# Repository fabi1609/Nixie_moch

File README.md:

# Nixie_moch

You are not permitted to use this design commercially.
This work is licensed under a Attribution-NonCommercial-ShareAlike 4.0 International (CC BY-NC-SA 4.0) License.

## Description

This is a tiny IN-12 Nixie clock based on STM32. Every SMD component is placed on the bottom side of the PCB. Hardware works with 5 V USB power supply. Boost converter is regulated and driven by STM32.
This project is in beta phase.

## TODO: Write explanation

You are not permitted to use this design commercially.
This work is licensed under a Attribution-NonCommercial-ShareAlike 4.0 International (CC BY-NC-SA 4.0) License.

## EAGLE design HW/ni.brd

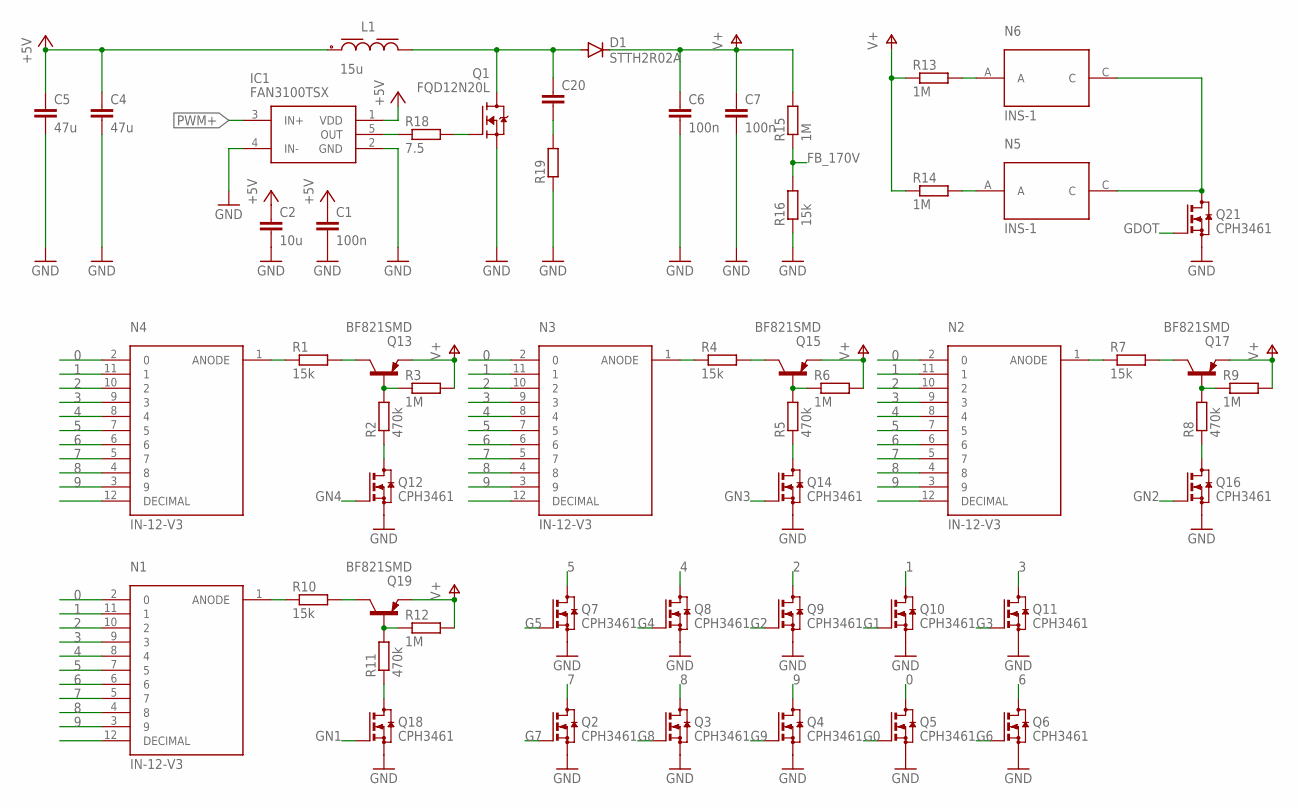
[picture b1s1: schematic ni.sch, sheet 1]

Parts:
C1: 100n; C0402
C2: 10u; C1206
C4, C5: 47u; C1206
C6, C7: 100n; C1812
C20: C-EUC1206; C1206
D1: STTH2R02A; DO214AC
IC1: FAN3100TSX; SOT95P280X145-5N
L1: 15u; WE-LQS_5040
N1, N2, N3, N4: IN-12-V3; IN-12
N5, N6: INS-1
Q1: FQD12N20L; TO229P990X240-3N
Q2, Q3, Q4, Q5, Q6, Q7, Q8, Q9, Q10, Q11, Q12, Q14, Q16, Q18, Q21: CPH3461; SOT23
Q13, Q15, Q17, Q19: BF821SMD; SOT23-BEC
R1, R4, R7, R10: 15k; R1206
R2, R5, R8, R11: 470k; R1206
R3, R6, R9, R12, R15: 1M; R1206
R13, R14: 1M; R2010
R16: 15k; R0402
R18: 7.5; R0603
R19: R-EU_R1206; R1206

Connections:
0: N1.2 (0), N2.2 (0), N3.2 (0), N4.2 (0), Q5.3 (D)
1: N1.11 (1), N2.11 (1), N3.11 (1), N4.11 (1), Q10.3 (D)
2: N1.10 (2), N2.10 (2), N3.10 (2), N4.10 (2), Q9.3 (D)
3: N1.9 (3), N2.9 (3), N3.9 (3), N4.9 (3), Q11.3 (D)
4: N1.8 (4), N2.8 (4), N3.8 (4), N4.8 (4), Q8.3 (D)
5: N1.7 (5), N2.7 (5), N3.7 (5), N4.7 (5), Q7.3 (D)
6: N1.6, N2.6, N3.6, N4.6, Q6.3 (D)
7: N1.5 (7), N2.5 (7), N3.5 (7), N4.5 (7), Q2.3 (D)
8: N1.4 (8), N2.4 (8), N3.4 (8), N4.4 (8), Q3.3 (D)
9: N1.3 (9), N2.3 (9), N3.3 (9), N4.3 (9), Q4.3 (D)
+5V: C1.1, C2.1, C4.1, C5.1, IC1.1 (VDD), L1.1; also elsewhere on the board
FB_170V: R15.1, R16.2; also elsewhere on the board
G0: Q5.1 (G); also elsewhere on the board
G1: Q10.1 (G); also elsewhere on the board
G2: Q9.1 (G); also elsewhere on the board
G3: Q11.1 (G); also elsewhere on the board
G4: Q8.1 (G); also elsewhere on the board
G5: Q7.1 (G); also elsewhere on the board
G6: Q6.1 (G); also elsewhere on the board
G7: Q2.1 (G); also elsewhere on the board
G8: Q3.1 (G); also elsewhere on the board
G9: Q4.1 (G); also elsewhere on the board
GDOT: Q21.1 (G); also elsewhere on the board
GN1: Q18.1 (G); also elsewhere on the board
GN2: Q16.1 (G); also elsewhere on the board
GN3: Q14.1 (G); also elsewhere on the board
GN4: Q12.1 (G); also elsewhere on the board
GND: C1.2, C2.2, C4.2, C5.2, C6.2, C7.2, IC1.2 (GND), IC1.4 (IN-), Q1.2 (S), Q2.2 (S), Q3.2 (S), Q4.2 (S), Q5.2 (S), Q6.2 (S), Q7.2 (S), Q8.2 (S), Q9.2 (S), Q10.2 (S), Q11.2 (S), Q12.2 (S), Q14.2 (S), Q16.2 (S), Q18.2 (S), Q21.2 (S), R16.1, R19.1; also elsewhere on the board
unnamed: C20.1, D1.A, L1.2, Q1.3 (D)
unnamed: Q1.1 (G), R18.2
unnamed: N3.1 (ANODE), R4.1
unnamed: N4.1 (ANODE), R1.1
unnamed: Q13.C, R1.2
unnamed: Q13.B, R2.2, R3.1
unnamed: Q12.3 (D), R2.1
unnamed: Q15.C, R4.2
unnamed: N5.C, N6.C, Q21.3 (D)
unnamed: N6.A, R13.2
unnamed: Q15.B, R5.2, R6.1
unnamed: Q14.3 (D), R5.1
unnamed: N2.1 (ANODE), R7.1
unnamed: IC1.5 (OUT), R18.1
unnamed: Q17.C, R7.2
unnamed: Q17.B, R8.2, R9.1
unnamed: C20.2, R19.2
unnamed: Q16.3 (D), R8.1
unnamed: N1.1 (ANODE), R10.1
unnamed: Q19.C, R10.2
unnamed: Q19.B, R11.2, R12.1
unnamed: Q18.3 (D), R11.1
unnamed: N5.A, R14.2
PWM+: IC1.3 (IN+); also elsewhere on the board
V+: C6.1, C7.1, D1.C, Q13.E, Q15.E, Q17.E, Q19.E, R3.2, R6.2, R9.2, R12.2, R13.1, R14.1, R15.2

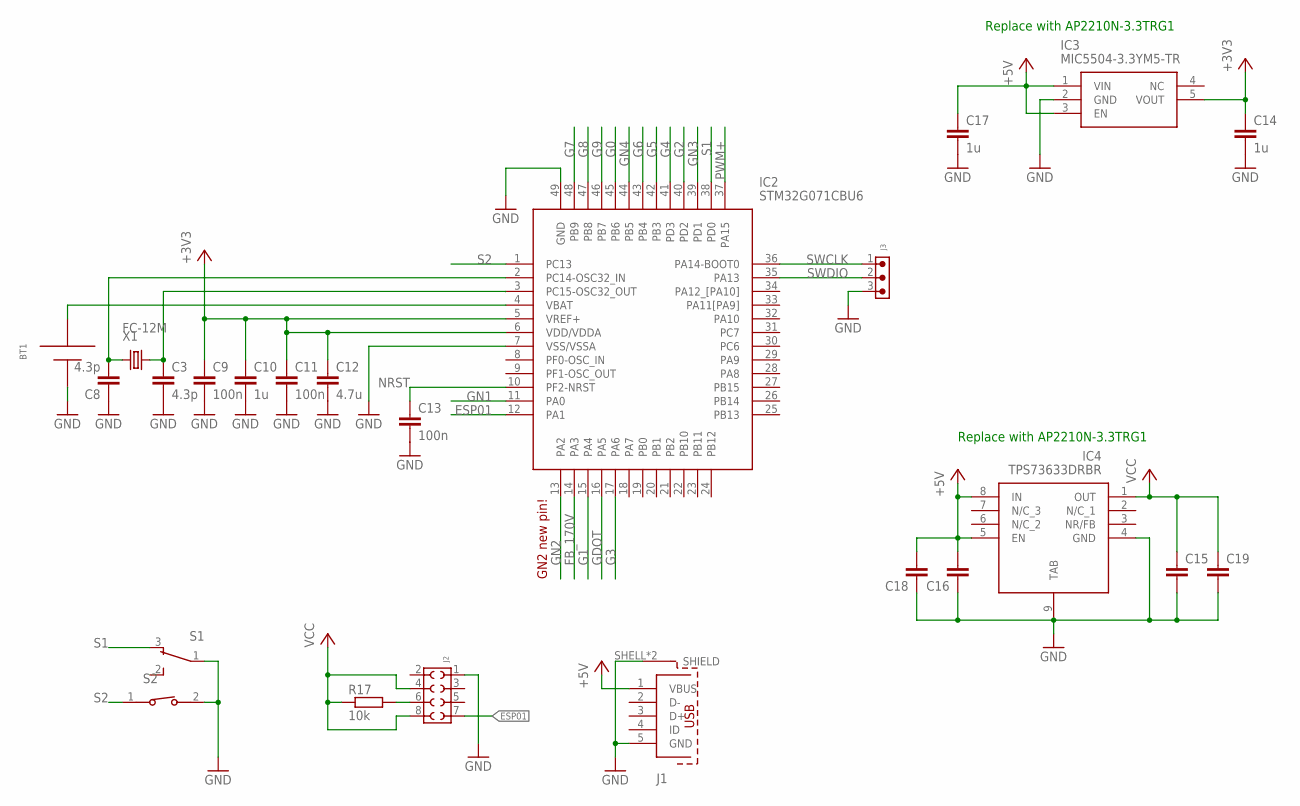
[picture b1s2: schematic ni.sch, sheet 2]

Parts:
BT1: CR1225FH-LF
C3, C8: 4.3p; C0402
C9, C11, C13: 100n; C0402
C10, C14: 1u; C0402
C12: 4.7u; C0402
C15, C16: C-EUC1206; C1206
C17: 1u; C0603
C18, C19: C-EUC0603; C0603
IC2: STM32G071CBU6; QFN50P700X700X60-49N
IC3: MIC5504-3.3YM5-TR; SOT95P280X145-5N
IC4: TPS73633DRBR; SON65P300X300X100-9N
J1: 614105150721
J2: 6100XX21821_61000821821; 61000821821
J3: OWN_3PIN; OWN-3PIN
R17: 10k; R0402
S1: 450301014042
S2: 434121050816
X1: FC-12M

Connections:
+3V3: C9.1, C10.1, C11.1, C12.1, C14.1, IC2.5 (VREF+), IC2.6 (VDD/VDDA), IC3.5 (VOUT)
+5V: C16.2, C17.1, C18.2, IC3.1 (VIN), IC3.3 (EN), IC4.5 (EN), IC4.8 (IN), J1.1 (VBUS); also elsewhere on the board
ESP01: IC2.12 (PA1), J2.7
FB_170V: IC2.14 (PA3); also elsewhere on the board
G0: IC2.45 (PB6); also elsewhere on the board
G1: IC2.15 (PA4); also elsewhere on the board
G2: IC2.40 (PD2); also elsewhere on the board
G3: IC2.17 (PA6); also elsewhere on the board
G4: IC2.41 (PD3); also elsewhere on the board
G5: IC2.42 (PB3); also elsewhere on the board
G6: IC2.43 (PB4); also elsewhere on the board
G7: IC2.48 (PB9); also elsewhere on the board
G8: IC2.47 (PB8); also elsewhere on the board
G9: IC2.46 (PB7); also elsewhere on the board
GDOT: IC2.16 (PA5); also elsewhere on the board
GN1: IC2.11 (PA0); also elsewhere on the board
GN2: IC2.13 (PA2); also elsewhere on the board
GN3: IC2.39 (PD1); also elsewhere on the board
GN4: IC2.44 (PB5); also elsewhere on the board
GND: BT1.-, C3.2, C8.1, C9.2, C10.2, C11.2, C12.2, C13.2, C14.2, C15.2, C16.1, C17.2, C18.1, C19.2, IC2.7 (VSS/VSSA), IC2.49 (GND), IC3.2 (GND), IC4.4 (GND), IC4.9 (TAB), J1.5 (GND), J1.SHELL (SHIELD), J1.SHELL1 (SHIELD), J2.1, J3.3, S1.1, S2.2; also elsewhere on the board
unnamed: J2.6, R17.2
unnamed: BT1.+, IC2.4 (VBAT)
unnamed: C3.1, IC2.3 (PC15-OSC32_OUT), X1.2
unnamed: C8.2, IC2.2 (PC14-OSC32_IN), X1.1
NRST: C13.1, IC2.10 (PF2-NRST)
PWM+: IC2.37 (PA15); also elsewhere on the board
S1: IC2.38 (PD0), S1.3
S2: IC2.1 (PC13), S2.1
SWCLK: IC2.36 (PA14-BOOT0), J3.1
SWDIO: IC2.35 (PA13), J3.2
VCC: C15.1, C19.1, IC4.1 (OUT), J2.4, J2.8, R17.1

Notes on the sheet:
GN2 new pin!
Replace with AP2210N-3.3TRG1

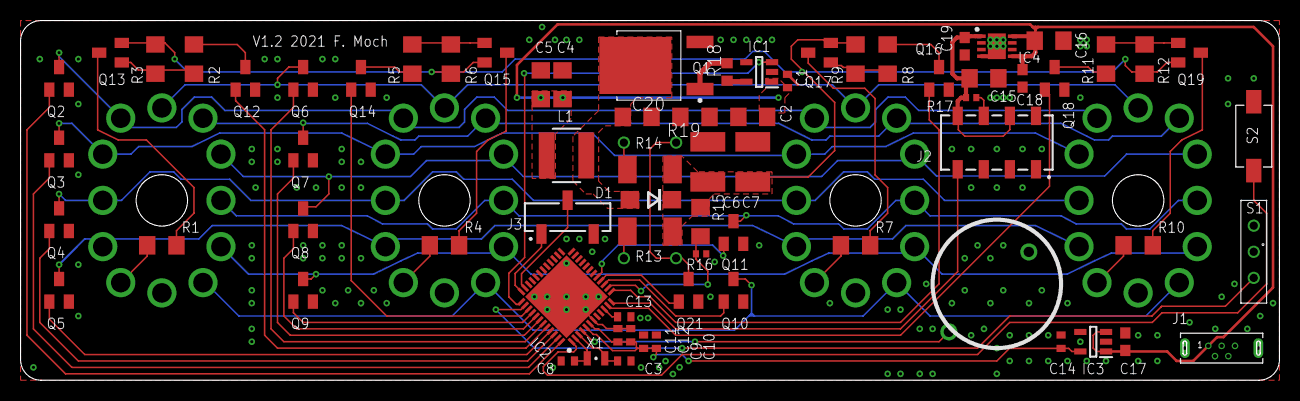
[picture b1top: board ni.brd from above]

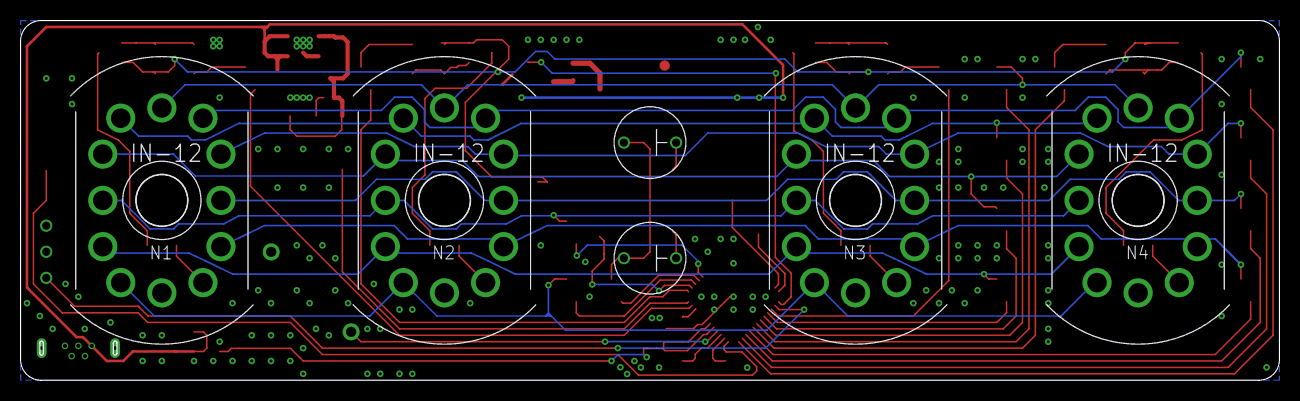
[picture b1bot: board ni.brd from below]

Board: 2 copper layers, 122.4 x 34.9 mm, 78 parts (6 on the bottom side), 65 nets.

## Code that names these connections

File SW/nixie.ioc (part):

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Mcu.Name=STM32G071C(6-8-B)Ux
Mcu.Package=UFQFPN48
Mcu.UserName=STM32G071CBUx
PA0.GPIOParameters=GPIO_Label
PA0.GPIO_Label=GN1
PA0.Signal=GPIO_Output
PA1.GPIOParameters=GPIO_PuPd,GPIO_Label,GPIO_ModeDefaultEXTI
PA1.GPIO_Label=ESP01
PA1.GPIO_ModeDefaultEXTI=GPIO_MODE_IT_FALLING
PA1.GPIO_PuPd=GPIO_PULLUP
PA1.Signal=GPXTI1
PA10.Signal=GPIO_Output
PA11\ [PA9].Signal=GPIO_Output
PA12\ [PA10].Signal=GPIO_Output
PA13.Mode=Serial_Wire
PA13.Signal=SYS_SWDIO
PA14-BOOT0.Mode=Serial_Wire
PA14-BOOT0.Signal=SYS_SWCLK
PA15.GPIOParameters=GPIO_Speed
PA15.GPIO_Speed=GPIO_SPEED_FREQ_MEDIUM
PA15.Signal=S_TIM2_CH1
PA2.GPIOParameters=GPIO_Label
PA2.GPIO_Label=GN2
PA2.Signal=GPIO_Output
PA3.GPIOParameters=GPIO_Label
PA3.GPIO_Label=FB_170V
PA3.Mode=INP
PA3.Signal=COMP2_INP
PA4.GPIOParameters=GPIO_Label
PA4.GPIO_Label=G1
PA4.Signal=GPIO_Output
PA5.GPIOParameters=GPIO_PuPd,GPIO_Label
PA5.GPIO_Label=GDOT
PA5.GPIO_PuPd=GPIO_PULLDOWN
PA5.Signal=GPIO_Output
PA6.GPIOParameters=GPIO_Label
PA6.GPIO_Label=G3
PA6.Signal=GPIO_Output
PA7.Signal=GPIO_Output
PA8.Signal=GPIO_Output
PA9.Signal=GPIO_Output
PB0.Signal=GPIO_Output
PB1.Signal=GPIO_Output
PB10.Signal=GPIO_Output
PB11.Signal=GPIO_Output
PB12.Signal=GPIO_Output
PB13.Signal=GPIO_Output
PB14.Signal=GPIO_Output
PB15.Signal=GPIO_Output
PB2.Signal=GPIO_Output
PB3.GPIOParameters=GPIO_Label
PB3.GPIO_Label=G5
PB3.Signal=GPIO_Output
PB4.GPIOParameters=GPIO_Label
PB4.GPIO_Label=G6
PB4.Signal=GPIO_Output
PB5.GPIOParameters=GPIO_Label
PB5.GPIO_Label=GN4
PB5.Signal=GPIO_Output
PB6.GPIOParameters=GPIO_Label
PB6.GPIO_Label=G0
PB6.Signal=GPIO_Output
PB7.GPIOParameters=GPIO_Label
PB7.GPIO_Label=G9
PB7.Signal=GPIO_Output
PB8.GPIOParameters=GPIO_Label
PB8.GPIO_Label=G8
PB8.Signal=GPIO_Output
PB9.GPIOParameters=GPIO_Label
PB9.GPIO_Label=G7
PB9.Signal=GPIO_Output
PC13.GPIOParameters=GPIO_PuPd,GPIO_Label
PC13.GPIO_Label=S2
PC13.GPIO_PuPd=GPIO_PULLUP
PC13.Signal=GPIO_Input
PC14-OSC32_IN\ (PC14).Mode=LSE-External-Oscillator
PC14-OSC32_IN\ (PC14).Signal=RCC_OSC32_IN
PC15-OSC32_OUT\ (PC15).Mode=LSE-External-Oscillator
PC15-OSC32_OUT\ (PC15).Signal=RCC_OSC32_OUT
PC6.Signal=GPIO_Output
PC7.Signal=GPIO_Output
PD0.GPIOParameters=GPIO_PuPd,GPIO_Label
PD0.GPIO_Label=S1
PD0.GPIO_PuPd=GPIO_PULLUP
PD0.Signal=GPIO_Input
PD1.GPIOParameters=GPIO_Label
PD1.GPIO_Label=GN3
PD1.Signal=GPIO_Output
PD2.GPIOParameters=GPIO_Label
PD2.GPIO_Label=G2
PD2.Signal=GPIO_Output
PD3.GPIOParameters=GPIO_Label
PD3.GPIO_Label=G4
PD3.Signal=GPIO_Output
PF0-OSC_IN\ (PF0).Signal=GPIO_Output
PF1-OSC_OUT\ (PF1).Signal=GPIO_Output
PF2\ -\ NRST.GPIOParameters=GPIO_Label
PF2\ -\ NRST.GPIO_Label=NRST
PF2\ -\ NRST.Signal=GPIO_Input
RCC.HSE_VALUE=8000000
RCC.SYSCLKFreq_VALUE=64000000
RCC.SYSCLKSource=RCC_SYSCLKSOURCE_PLLCLK
board=custom

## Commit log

2019-10-22 initial
2019-10-22 Neu sortiert
2019-10-22 STM32_init
2019-10-26 GPIOs labeled
2019-10-28 timers configuration
2019-10-29 Grundgerüst_zwischenstand
2019-10-31 HW_values added
2019-11-05 basic programm without clock
2019-11-08 CPU to 64 MHz and one shot timer setting
2019-11-08 activatet pullups and activatet forgotten interrupt
2019-11-12 Set target voltage
2019-11-13 Nixie working; Comp start; Faster boost start; Multiplex error fixed
2019-11-13 nixie working
2019-11-14 working clock without alarm
2019-11-14 HW V1.1 fixed 3.3V supply
2019-11-15 Revert "working clock without alarm"
    This reverts commit 98b262ec7a724c22e952bbc001f03cf0f60239ae.
2019-11-15 V1.1 fixed nixie footprint
2019-11-15 Project cleaned
2019-11-16 changed button logic and set voltage to 145V
2019-11-17 Zwischenstand zu V1.1 Revision
2019-11-22 V1.1 revertet to old nixie footprint for socket mounting
2019-12-14 crystal high drive
2019-12-15 README.md
2019-12-15 added docu
2019-12-15 added pictures
2019-12-23 dcf77
2019-12-23 dcf77 working
2020-01-29 WIFI added
2020-02-13 new sw init for wifi
2020-02-14 implemented readout of ESP01 Module
2020-02-15 clock.h, clock.c und main.c aktualisiert
2020-03-09 ni.brd, ni.sch und 13 weitere dateien aktualisiert...
2021-02-26 New method for wifi read
2021-02-27 Added scheduled reset feature
2021-02-27 bugfix
2021-02-27 WIFI RESET Version
2021-11-15 working on snubber design
2022-02-12 rc snubber

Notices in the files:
README.md:
License: CC BY-NC-SA 4.0
parts and their libraries:
Wurth_Elektronik_Passive_rev19e: Copyright: Würth Elektronik
